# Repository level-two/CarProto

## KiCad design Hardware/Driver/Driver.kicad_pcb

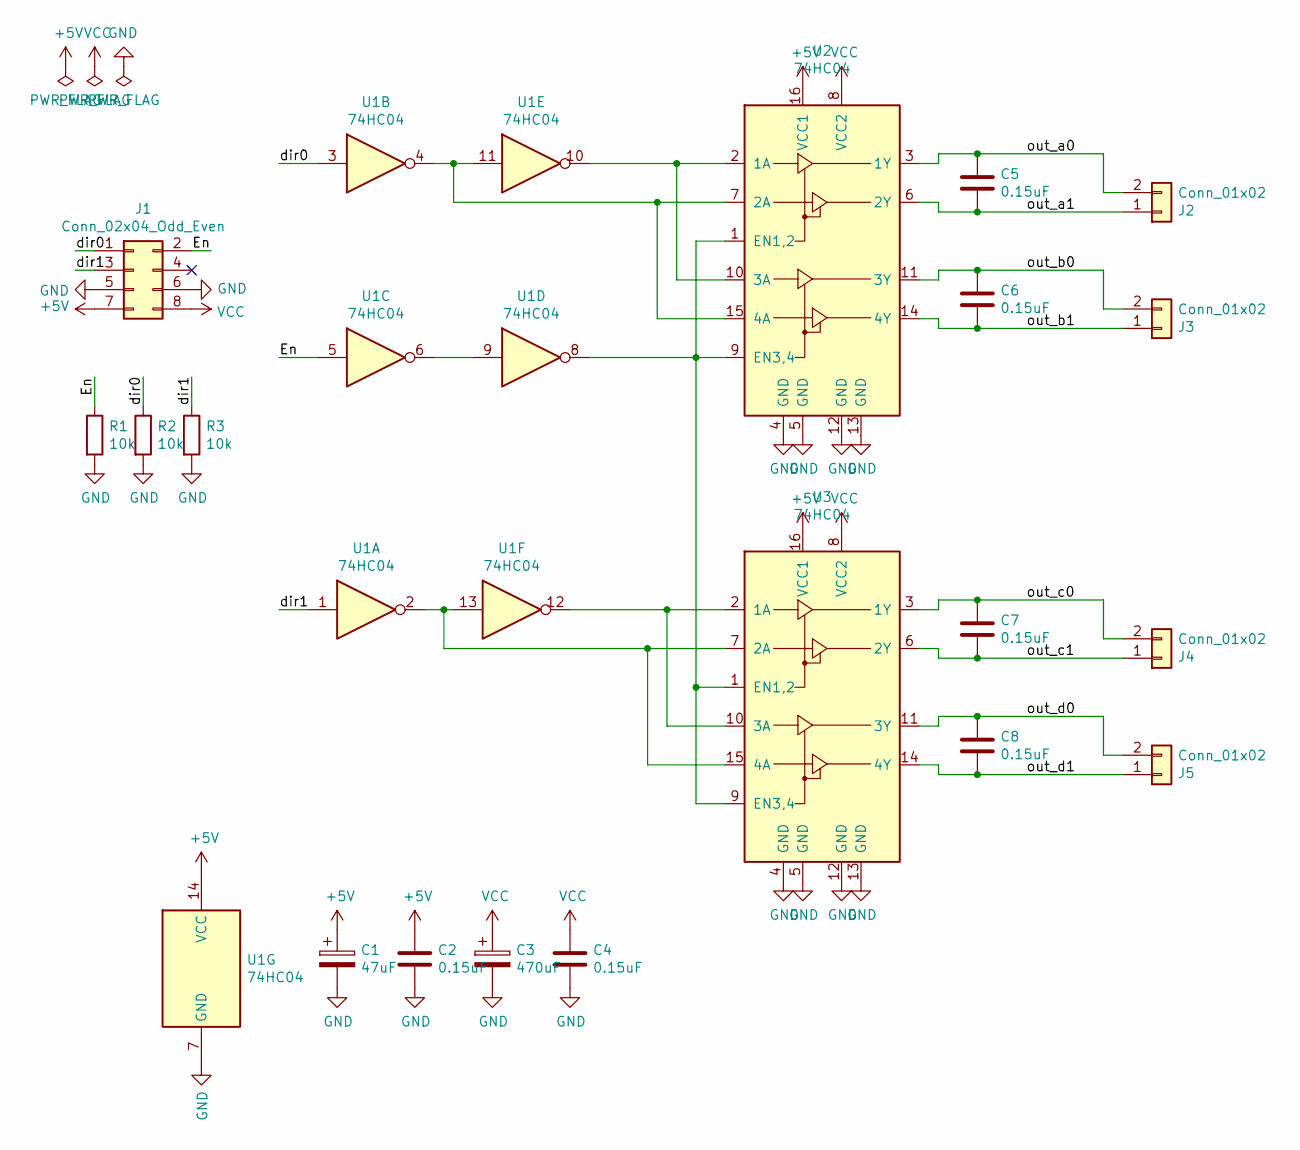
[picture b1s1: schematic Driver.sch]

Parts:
C1: 47uF; CP_Radial_D5.0mm_P2.50mm
C2, C4, C5, C6, C7, C8: 0.15uF; C_Rect_L7.0mm_W2.5mm_P5.00mm
C3: 470uF; CP_Radial_D10.0mm_P5.00mm
J1: Conn_02x04_Odd_Even; PinHeader_2x04_P2.54mm_Horizontal
J2, J3, J4, J5: Conn_01x02; PinHeader_1x02_P2.54mm_Horizontal
R1, R2, R3: 10k; R_Axial_DIN0204_L3.6mm_D1.6mm_P7.62mm_Horizontal
U1: 74HC04; DIP-14_W7.62mm
U2, U3: 74HC04; DIP-16_W7.62mm

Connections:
+5V: C1.1, C2.1, J1.7, U1.14 (VCC), U2.16 (VCC1), U3.16 (VCC1)
/En: J1.2, R1.1, U1.5
/dir0: J1.1, R2.1, U1.3
/dir1: J1.3, R3.1, U1.1
/out_a0: C5.1, J2.2, U2.3 (1Y)
/out_a1: C5.2, J2.1, U2.6 (2Y)
/out_b0: C6.1, J3.2, U2.11 (3Y)
/out_b1: C6.2, J3.1, U2.14 (4Y)
/out_c0: C7.1, J4.2, U3.3 (1Y)
/out_c1: C7.2, J4.1, U3.6 (2Y)
/out_d0: C8.1, J5.2, U3.11 (3Y)
/out_d1: C8.2, J5.1, U3.14 (4Y)
GND: C1.2, C2.2, C3.2, C4.2, J1.5, J1.6, R1.2, R2.2, R3.2, U1.7 (GND), U2.4 (GND), U2.5 (GND), U2.12 (GND), U2.13 (GND), U3.4 (GND), U3.5 (GND), U3.12 (GND), U3.13 (GND)
unnamed: U1.6, U1.9
unnamed: U1.8, U2.1 (EN1,2), U2.9 (EN3,4), U3.1 (EN1,2), U3.9 (EN3,4)
unnamed: U1.10, U2.2 (1A), U2.10 (3A)
unnamed: U1.4, U1.11, U2.7 (2A), U2.15 (4A)
unnamed: U1.12, U3.2 (1A), U3.10 (3A)
unnamed: U1.2, U1.13, U3.7 (2A), U3.15 (4A)
VCC: C3.1, C4.1, J1.8, U2.8 (VCC2), U3.8 (VCC2)

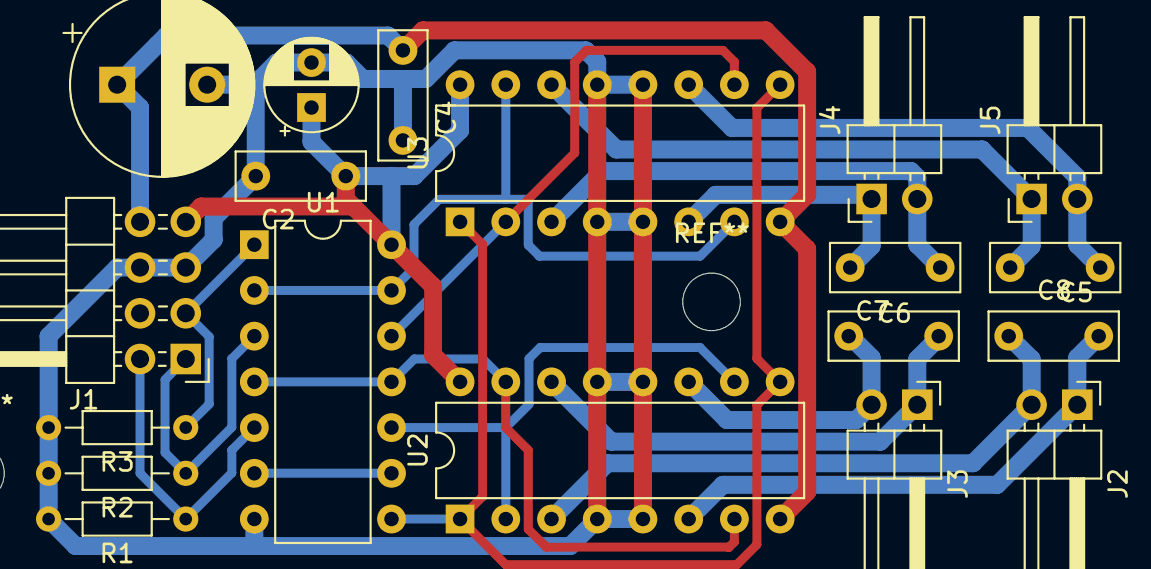
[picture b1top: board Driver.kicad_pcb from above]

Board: 2 copper layers, 19 parts (0 on the bottom side), 20 nets.

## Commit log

2020-05-05 +Project file and structure
    + UART configured to receive data from bluetooth and send it to UART0
    + avr-uart library linked from https://github.com/andygock/avr-uart
2020-05-06 Draft interfaces of the stepper subsystem layers
2020-05-09 Stepper driver implementation
    + Divided functionality into several layers
    + Added bitManipulations helpers
2020-05-11 Stepper driver implementation
2020-05-12 Fixed UART baud rate error
    Baud rate set error caused incorrect data reception of data packages
2020-05-15 Stepper protocol layer implementation
    - Implemented state machine
    - Implemented states
    - Transition between states
2020-05-19 Stepper driver structure
    - Configuration
    - Wiring
    - Possibility of handling multiple steppers
2020-05-20 Button implementation
2020-05-20 Refactoring
    - Independent stepper driver
    + placeholder for steer implementation
2020-05-20 Release for button and stepper
    Steer setup draft implementation
2020-05-21 Steer state machine draft implementation Refactoring: - Renamed states - Renamed functions to avoid name collisions
2020-05-22 Steer implementation
    - Implemented state machine
    - Implemented states and algorithms
2020-05-23 Timer implementation
    - Update cycle
    - Time lapsed since last cycle
2020-05-23 Simple commands
2020-05-26 - Sleep state during steer idle
    - Wiring
    - Improved stepper ports configuration to avoid glitches and incorrect mode
    - Fix: Sleep signal is inversed
2020-05-27 Fixes:
    - Command porcessing issue
    - Print busy status
2020-05-28 - Motor implementation
    - Refactoring
    - Raised warnings level to super-ultra-high
2020-05-29 i2c draft
2020-05-29 i2c implementation: - States machine with states - Transitions between states - Command and Command queue draft - Driver draft
2020-05-31 - Draft i2c command queue implementation - Transitions between states - Callback on completion with status
2020-07-03 i2c transaction state machine reworked
2020-07-03 - i2c transactions queue - compilation errors and warnings fixes
2020-07-04 Refactored i2c implementation in terms of operations on queue and its elements
2020-07-04 Code cleaned up a little bit
2020-07-04 i2c driver implementation
2020-07-04 - Integrated I2C driver with state machine - Added missed ReadAck and ReadNack states
2020-07-05 - i2c data read test - Code cleanup - Compilation issue fixed - Print error if F_CPU is not defined - which is implicitely reuqired by i2c and timer0 modules
2020-07-06 - Generic queue - Integrated queue into state machine and handle it in completion/idle states as well as provided default add method for new transactions
2020-07-09 - Ensure thread safety of the queue operation - Introduced initial state - Clear interrupt in preparation for data reception - Debug stuff
2020-07-09 Fix in the avr-uart library - restore interrupt state after atomic block instead of forcing it on
2020-07-10 - Forked avr-uart to own repo - Set TX UART buffer to 128 bytes
2020-07-10 Check completion callback for NULL
2020-07-12 - Reworked i2c transaction layer - Use sequence instead of state machine - Handle queue separately
2020-07-13 - Gyroscope implementation - L2G4200D Register map - Added i2cReadByte func - Memory leak fixed: Release read i2c data on unsuccessfull request
2020-07-15 Sensors - accelerometer and magnetometer
2020-07-15 - Free resources held by i2c submodule as well as disable hardware - Free sensor data before calling delegate because it is already copied and there is no reason of holding it so long
2020-07-15 - Added memdebug - Checking for dynamic allocated memory leaks
2020-07-22 - Reference counting mechanism - Autorelease pool
2020-07-22 Use reference counting mechanism across the project
2020-07-22 - Small (cosmetic) fixes in the reference counting code - i2c - removed queue flushing as i2cDisable actually waits until all transactions are completed - Cleaned test code from main.c
2021-01-05 - Moved Sources to Software folder - Created Hardware folder and put there Driver PCB sources
2021-01-08 - Moved car-proto to separate folder inside Software - Added simple motors control over bluetooth
2021-01-16 Driver PCB: - Changed footprint of capacitor on VCC - Rearranged supply filter capacitors - PCB cleanup
